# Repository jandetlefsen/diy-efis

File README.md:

# diy-efis
Experimental Aircraft Avionics based on CAN Aerospace

This repository is the public code and design store for the Kotuku Aerospace http://www.kotuku.aero contributed avionics project.

New: Facebook page created:

https://www.facebook.com/diyefis/

This project has designs from 2016 that have been tested.

The project has 3 core streams:

** diy-efis **
Portable C code that implements a full graphical display for avionics that can run on very low power devices.  The development environment is Eclipse on Linux or Visual Studio on Windows

** Embedded devices **
All diy-efis hardware devices are based on a common hardware family, the dsPIC33EP series from Microchip.  These devices are programmed in C and have the core I/O functions needed by the CANFly systems.  There is a common operating system and I/O drivers for most peripherals.

** Hardware Designs **
All diy-efis hardware designs are open source and are provided in Eagle PCB format.  They are designed to be very low cost 2 sided PCB's that can be hand assembled by a enthusiest.  Kotuku Aerospace will sell boards, partial kits, full kits or assembled hardware based on these designs.

diy-efis is managed by Kotuku Aerospace and any money made from selling kits is used to fund the hosting and designs.

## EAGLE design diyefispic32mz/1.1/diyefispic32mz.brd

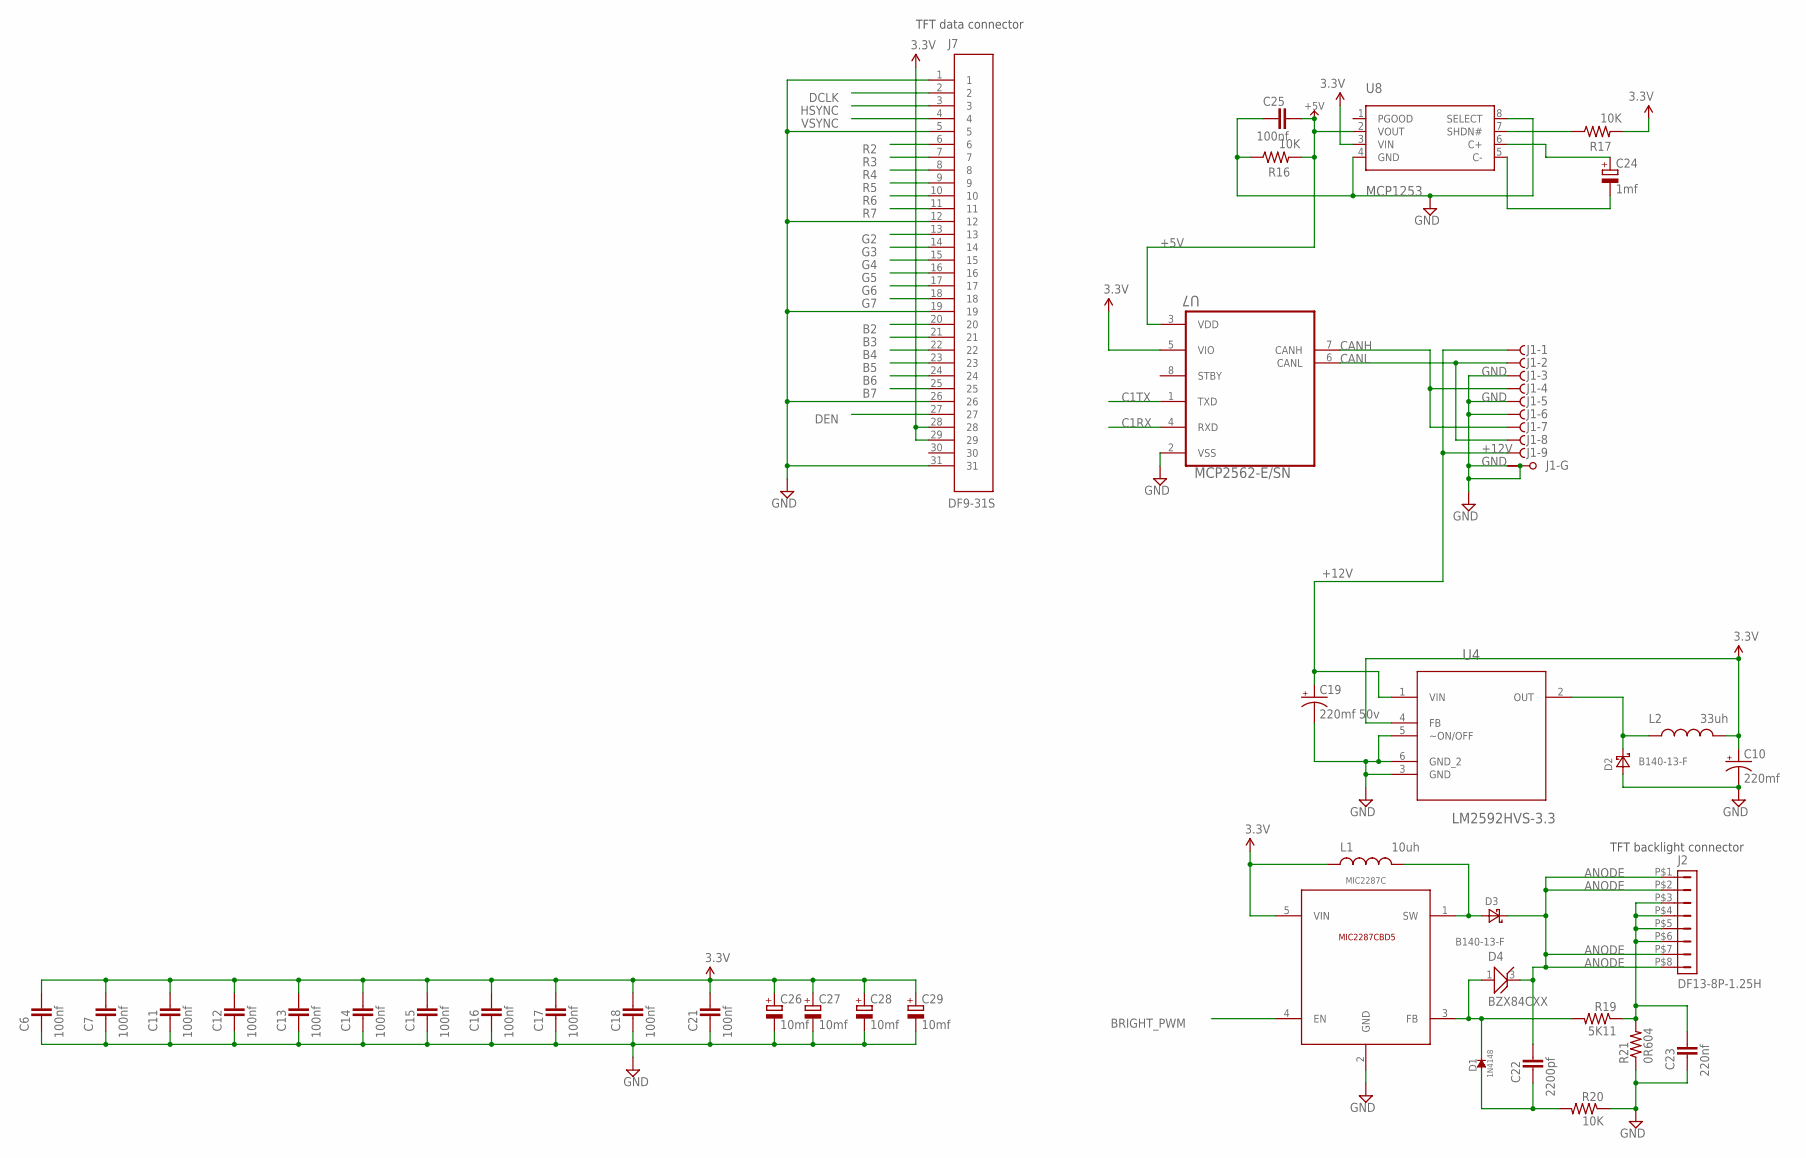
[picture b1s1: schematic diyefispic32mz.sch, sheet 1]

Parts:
C6, C7, C11, C12, C13, C14, C15, C16, C17, C18, C21, C25: 100nf; C805; PARTNO CL21F104ZBCNNNC
C10: 220mf; EIA7343; PARTNO T545X227M016ATE035
C19: 220mf 50v; EIA7343; PARTNO T545X227M016ATE035
C22: 2200pf; C805; PARTNO CL21B222KBANNNC
C23: 220nf; C805; PARTNO CL21F224ZBCNNNC
C24: 1mf; SMC_A; PARTNO F931C105MAA
C26, C27, C28, C29: 10mf; SMC_A; PARTNO T491A106K004AT
D1: 1N4148; SOD523; PARTNO 1N4148WT
D2, D3: B140-13-F; SMA; PARTNO B140-13-F
D4: BZX84CXX; SOT91P240X110-3N; PARTNO BZX84C30-7-F
J1: F09VPS; F09VP; PARTNO 3-1634222-2
J2: DF13-8P-1.25H; DF13A-8P-1.25H; PARTNO DF13A-8P-1.25H(50)
J7: DF9-31S; PARTNO DF9-31S-1V(32)
L1: 10uh; 1812; PARTNO VLF504015MT-100M
L2: 33uh; 1812; PARTNO LQH43MN330K03L
R16, R17, R20: 10K; 0603-RES; PARTNO RC0603FR-0710KL
R19: 5K11; 0603-RES; PARTNO RC0603FR-075K23L
R21: 0R604; 1812; PARTNO RL1218FK-070R604L
U4: LM2592HVS-3.3; TO170P1435X457-5N; PARTNO LM2592HVSX-3.3/NOPB
U7: MCP2562-E/SN; SOIC127P600X175-8N; PARTNO MCP2562-E/SN
U8: MCP1253; MSOP8; PARTNO MCP1253-33X50I/MS
U9: MIC2287C; SOT-23-5; PARTNO MIC2287CYD5-TR

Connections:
3.3V: C6.1, C7.1, C10.A (+), C11.1, C12.1, C13.1, C14.1, C15.1, C16.1, C17.1, C18.1, C21.1, C26.+, C27.+, C28.+, C29.+, J7.28, J7.29, L1.1, L2.2, R17.2, U4.4 (FB), U7.5 (VIO), U8.3 (VIN), U9.5 (VIN); also elsewhere on the board
+5V: C25.1, R16.2, U7.3 (VDD), U8.2 (VOUT); also elsewhere on the board
+12V: C19.A (+), J1.1 (F), J1.9 (F), U4.1 (VIN)
ANODE: C22.1, D3.C, D4.3 (CATHODE), J2.P$1 (1), J2.P$2 (2), J2.P$7 (7), J2.P$8 (8)
B2: J7.20; also elsewhere on the board
B3: J7.21; also elsewhere on the board
B4: J7.22; also elsewhere on the board
B5: J7.23; also elsewhere on the board
B6: J7.24; also elsewhere on the board
B7: J7.25; also elsewhere on the board
BRIGHT_PWM: U9.4 (EN); also elsewhere on the board
C1RX: U7.4 (RXD); also elsewhere on the board
C1TX: U7.1 (TXD); also elsewhere on the board
CANH: J1.4 (F), J1.7 (F), U7.7 (CANH)
CANL: J1.2 (F), J1.8 (F), U7.6 (CANL)
DCLK: J7.2; also elsewhere on the board
DEN: J7.27; also elsewhere on the board
G2: J7.13; also elsewhere on the board
G3: J7.14; also elsewhere on the board
G4: J7.15; also elsewhere on the board
G5: J7.16; also elsewhere on the board
G6: J7.17; also elsewhere on the board
G7: J7.18; also elsewhere on the board
GND: C6.2, C7.2, C10.C (-), C11.2, C12.2, C13.2, C14.2, C15.2, C16.2, C17.2, C18.2, C19.C (-), C21.2, C23.2, C25.2, C26.-, C27.-, C28.-, C29.-, D2.A, J1.3 (F), J1.5 (F), J1.6 (F), J1.G1, J1.G2, J7.1, J7.5, J7.12, J7.19, J7.26, J7.31, R16.1, R20.1, R21.1, U4.3 (GND), U4.5 (~ON/OFF), U4.6 (GND_2), U7.2 (VSS), U8.4 (GND), U8.8 (SELECT), U9.2 (GND); also elsewhere on the board
HSYNC: J7.3; also elsewhere on the board
unnamed: C23.1, J2.P$3 (3), J2.P$4 (4), J2.P$5 (5), J2.P$6 (6), R19.1, R21.2
unnamed: D2.C, L2.1, U4.2 (OUT)
unnamed: R17.1, U8.7 (SHDN#)
unnamed: C24.-, U8.5 (C-)
unnamed: C24.+, U8.6 (C+)
unnamed: D3.A, L1.2, U9.1 (SW)
unnamed: D1.C, D4.1 (ANODE), R19.2, U9.3 (FB)
unnamed: C22.2, D1.A, R20.2
R2: J7.6; also elsewhere on the board
R3: J7.7; also elsewhere on the board
R4: J7.8; also elsewhere on the board
R5: J7.9; also elsewhere on the board
R6: J7.10; also elsewhere on the board
R7: J7.11; also elsewhere on the board
VSYNC: J7.4; also elsewhere on the board

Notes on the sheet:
TFT data connector
TFT backlight connector

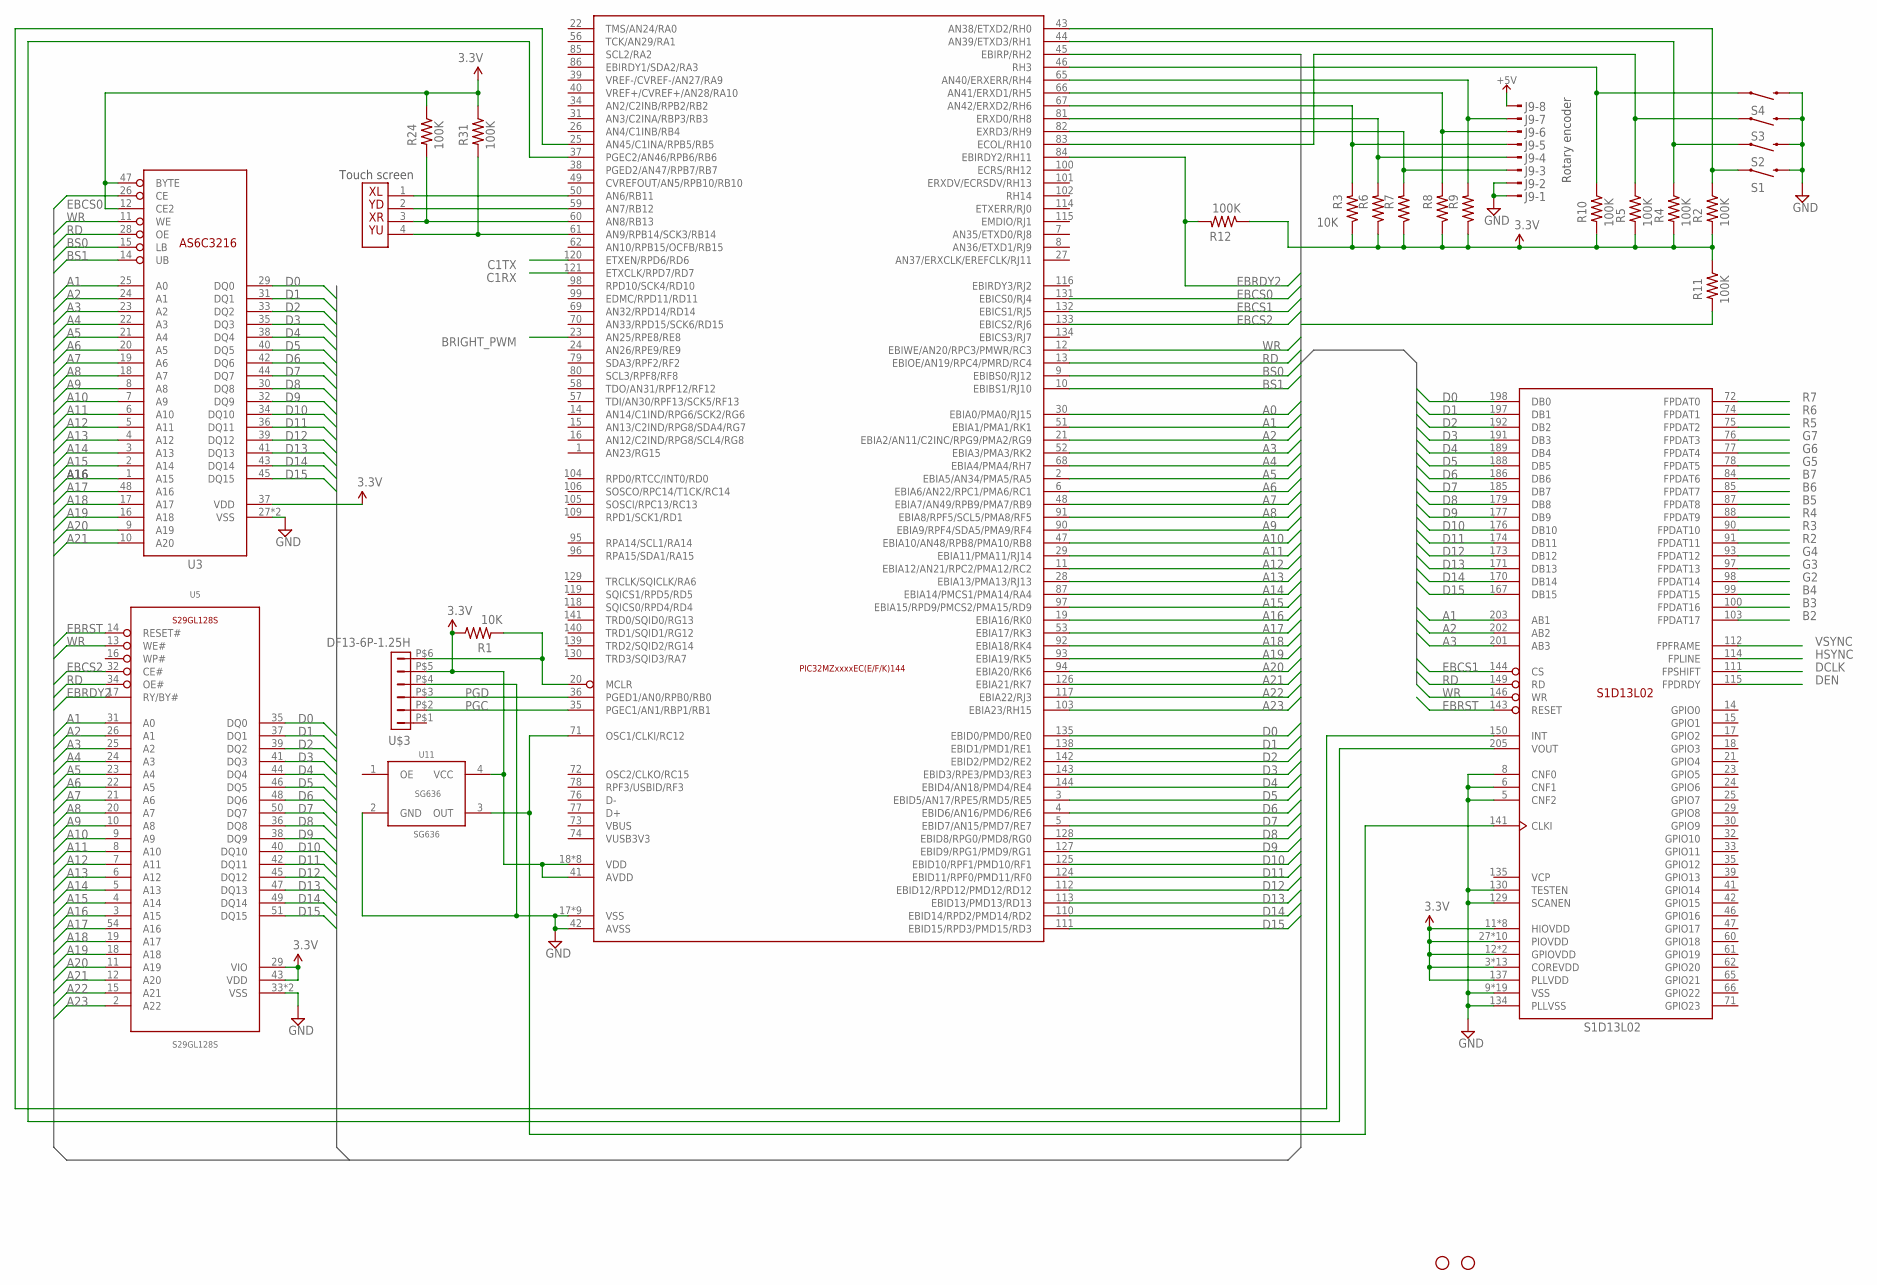
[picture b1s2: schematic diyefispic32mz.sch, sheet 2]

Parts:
J3: XF3M(1)-0415-1B; PARTNO XF3M(1)-0415-1B
J9: MTOP-8; PARTNO 7-215079-8
R1, R3, R6, R7, R8, R9: 10K; 0603-RES; PARTNO RC0603FR-0710KL
R2, R4, R5, R10, R11, R24, R31: 100K; 0603-RES; PARTNO RC0603JR-07100KL
R12: 100K; 0603-RES; PARTNO RC0603FR-0710KL
S1, S2, S3, S4: SWITCH-MOMENTARY-2SMD-4; TACTILE_SWITCH_TALL; PARTNO MJTP1138BTR
STANDOFF1, STANDOFF2: STAND-OFF; PARTNO *
U1: PIC32MZXXXXEC(E/F/K)144; TQFP-144; PARTNO PIC32MZ2048ECH144-I/PH
U2: S1D13L02; QFP208; PARTNO S1D13L02F00A100
U3: AS6C3216; TSOP48; PARTNO AS6C3216-55TIN
U5: S29GL128S; TSOP-56; PARTNO S29GL128S90TFI010
U11: SG636; PARTNO SG-636PCE 10.000MHZ
U$3: DF13-6P-1.25H; DF13A-6P-1.25H; PARTNO DF13A-6P-1.25H(20)

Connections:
3.3V: R1.1, R2.2, R3.1, R4.2, R5.2, R6.1, R7.1, R8.1, R9.1, R10.2, R11.1, R12.1, R24.1, R31.1, U1.18 (VDD), U1.33 (VDD), U1.41 (AVDD), U1.55 (VDD), U1.64 (VDD), U1.88 (VDD), U1.107 (VDD), U1.122 (VDD), U1.137 (VDD), U2.3 (COREVDD), U2.11 (HIOVDD), U2.12 (GPIOVDD), U2.26 (GPIOVDD), U2.27 (PIOVDD), U2.36 (PIOVDD), U2.38 (COREVDD), U2.45 (COREVDD), U2.48 (PIOVDD), U2.59 (PIOVDD), U2.68 (PIOVDD), U2.79 (PIOVDD), U2.82 (COREVDD), U2.94 (COREVDD), U2.96 (PIOVDD), U2.106 (PIOVDD), U2.119 (COREVDD), U2.121 (PIOVDD), U2.127 (PIOVDD), U2.128 (COREVDD), U2.133 (COREVDD), U2.137 (PLLVDD), U2.138 (HIOVDD), U2.148 (HIOVDD), U2.151 (HIOVDD), U2.152 (COREVDD), U2.157 (HIOVDD), U2.163 (COREVDD), U2.168 (HIOVDD), U2.181 (COREVDD), U2.184 (HIOVDD), U2.194 (COREVDD), U2.204 (COREVDD), U2.208 (HIOVDD), U3.12 (CE2), U3.37 (VDD), U3.47 (BYTE), U5.29 (VIO), U5.43 (VDD), U11.4 (VCC), U$3.P$5 (5); also elsewhere on the board
!MCLR: R1.2, U1.20 (MCLR), U$3.P$6 (6)
+5V: J9.8; also elsewhere on the board
A0: U1.30 (EBIA0/PMA0/RJ15)
A1: U1.51 (EBIA1/PMA1/RK1), U2.203 (AB1), U3.25 (A0), U5.31 (A0)
A2: U1.21 (EBIA2/AN11/C2INC/RPG9/PMA2/RG9), U2.202 (AB2), U3.24 (A1), U5.26 (A1)
A3: U1.52 (EBIA3/PMA3/RK2), U2.201 (AB3), U3.23 (A2), U5.25 (A2)
A4: U1.68 (EBIA4/PMA4/RH7), U3.22 (A3), U5.24 (A3)
A5: U1.2 (EBIA5/AN34/PMA5/RA5), U3.21 (A4), U5.23 (A4)
A6: U1.6 (EBIA6/AN22/RPC1/PMA6/RC1), U3.20 (A5), U5.22 (A5)
A7: U1.48 (EBIA7/AN49/RPB9/PMA7/RB9), U3.19 (A6), U5.21 (A6)
A8: U1.91 (EBIA8/RPF5/SCL5/PMA8/RF5), U3.18 (A7), U5.20 (A7)
A9: U1.90 (EBIA9/RPF4/SDA5/PMA9/RF4), U3.8 (A8), U5.10 (A8)
A10: U1.47 (EBIA10/AN48/RPB8/PMA10/RB8), U3.7 (A9), U5.9 (A9)
A11: U1.29 (EBIA11/PMA11/RJ14), U3.6 (A10), U5.8 (A10)
A12: U1.11 (EBIA12/AN21/RPC2/PMA12/RC2), U3.5 (A11), U5.7 (A11)
A13: U1.28 (EBIA13/PMA13/RJ13), U3.4 (A12), U5.6 (A12)
A14: U1.87 (EBIA14/PMCS1/PMA14/RA4), U3.3 (A13), U5.5 (A13)
A15: U1.97 (EBIA15/RPD9/PMCS2/PMA15/RD9), U3.2 (A14), U5.4 (A14)
A16: U1.19 (EBIA16/RK0), U3.1 (A15), U5.3 (A15)
A17: U1.53 (EBIA17/RK3), U3.48 (A16), U5.54 (A16)
A18: U1.92 (EBIA18/RK4), U3.17 (A17), U5.19 (A17)
A19: U1.93 (EBIA19/RK5), U3.16 (A18), U5.18 (A18)
A20: U1.94 (EBIA20/RK6), U3.9 (A19), U5.11 (A19)
A21: U1.126 (EBIA21/RK7), U3.10 (A20), U5.12 (A20)
A22: U1.117 (EBIA22/RJ3), U5.15 (A21)
A23: U1.103 (EBIA23/RH15), U5.2 (A22)
B2: U2.103 (FPDAT17); also elsewhere on the board
B3: U2.100 (FPDAT16); also elsewhere on the board
B4: U2.99 (FPDAT15); also elsewhere on the board
B5: U2.87 (FPDAT8); also elsewhere on the board
B6: U2.85 (FPDAT7); also elsewhere on the board
B7: U2.84 (FPDAT6); also elsewhere on the board
BRIGHT_PWM: U1.23 (AN25/RPE8/RE8); also elsewhere on the board
BS0: U1.9 (EBIBS0/RJ12), U3.15 (LB)
BS1: U1.10 (EBIBS1/RJ10), U3.14 (UB)
C1RX: U1.121 (ETXCLK/RPD7/RD7); also elsewhere on the board
C1TX: U1.120 (ETXEN/RPD6/RD6); also elsewhere on the board
D0: U1.135 (EBID0/PMD0/RE0), U2.198 (DB0), U3.29 (DQ0), U5.35 (DQ0)
D1: U1.138 (EBID1/PMD1/RE1), U2.197 (DB1), U3.31 (DQ1), U5.37 (DQ1)
D2: U1.142 (EBID2/PMD2/RE2), U2.192 (DB2), U3.33 (DQ2), U5.39 (DQ2)
D3: U1.143 (EBID3/RPE3/PMD3/RE3), U2.191 (DB3), U3.35 (DQ3), U5.41 (DQ3)
D4: U1.144 (EBID4/AN18/PMD4/RE4), U2.189 (DB4), U3.38 (DQ4), U5.44 (DQ4)
D5: U1.3 (EBID5/AN17/RPE5/RMD5/RE5), U2.188 (DB5), U3.40 (DQ5), U5.46 (DQ5)
D6: U1.4 (EBID6/AN16/PMD6/RE6), U2.186 (DB6), U3.42 (DQ6), U5.48 (DQ6)
D7: U1.5 (EBID7/AN15/PMD7/RE7), U2.185 (DB7), U3.44 (DQ7), U5.50 (DQ7)
D8: U1.128 (EBID8/RPG0/PMD8/RG0), U2.179 (DB8), U3.30 (DQ8), U5.36 (DQ8)
D9: U1.127 (EBID9/RPG1/PMD9/RG1), U2.177 (DB9), U3.32 (DQ9), U5.38 (DQ9)
D10: U1.125 (EBID10/RPF1/PMD10/RF1), U2.176 (DB10), U3.34 (DQ10), U5.40 (DQ10)
D11: U1.124 (EBID11/RPF0/PMD11/RF0), U2.174 (DB11), U3.36 (DQ11), U5.42 (DQ11)
D12: U1.112 (EBID12/RPD12/PMD12/RD12), U2.173 (DB12), U3.39 (DQ12), U5.45 (DQ12)
D13: U1.113 (EBID13/PMD13/RD13), U2.171 (DB13), U3.41 (DQ13), U5.47 (DQ13)
D14: U1.110 (EBID14/RPD2/PMD14/RD2), U2.170 (DB14), U3.43 (DQ14), U5.49 (DQ14)
D15: U1.111 (EBID15/RPD3/PMD15/RD3), U2.167 (DB15), U3.45 (DQ15), U5.51 (DQ15)
DCLK: U2.111 (FPSHIFT); also elsewhere on the board
DEN: U2.115 (FPDRDY); also elsewhere on the board
EBCS0: U1.131 (EBICS0/RJ4), U3.26 (CE)
EBCS1: U1.132 (EBICS1/RJ5), U2.144 (CS)
EBCS2: U1.133 (EBICS2/RJ6), U5.32 (CE#)
EBRDY2: R12.2, U1.84 (EBIRDY2/RH11), U5.17 (RY/BY#)
EBRST: R11.2, U1.45 (EBIRP/RH2), U2.143 (RESET), U5.14 (RESET#)
G2: U2.98 (FPDAT14); also elsewhere on the board
G3: U2.97 (FPDAT13); also elsewhere on the board
G4: U2.93 (FPDAT12); also elsewhere on the board
G5: U2.78 (FPDAT5); also elsewhere on the board
G6: U2.77 (FPDAT4); also elsewhere on the board
G7: U2.76 (FPDAT3); also elsewhere on the board
GND: J9.1, J9.2, S1.B2 (2), S2.B2 (2), S3.B2 (2), S4.B2 (2), U1.17 (VSS), U1.32 (VSS), U1.42 (AVSS), U1.54 (VSS), U1.63 (VSS), U1.75 (VSS), U1.89 (VSS), U1.108 (VSS), U1.123 (VSS), U1.136 (VSS), U2.5 (CNF2), U2.6 (CNF1), U2.8 (CNF0), U2.9 (VSS), U2.20 (VSS), U2.28 (VSS), U2.44 (VSS), U2.50 (VSS), U2.58 (VSS), U2.69 (VSS), U2.80 (VSS), U2.95 (VSS), U2.109 (VSS), U2.120 (VSS), U2.129 (SCANEN), U2.130 (TESTEN), U2.132 (VSS), U2.134 (PLLVSS), U2.140 (VSS), U2.147 (VSS), U2.155 (VSS), U2.166 (VSS), U2.187 (VSS), U2.200 (VSS), U2.206 (VSS), U3.27 (VSS), U3.46 (VSS), U5.33 (VSS), U5.52 (VSS), U11.2 (GND), U$3.P$4 (4); also elsewhere on the board
GPG0: J9.7, R9.2, U1.65 (AN40/ERXERR/RH4)
GPG1: J9.6, R8.2, U1.66 (AN41/ERXD1/RH5)
GPG2: J9.3, R7.2, U1.82 (EXRD3/RH9)
GPG3: J9.4, R6.2, U1.81 (ERXD0/RH8)
GPG4: J9.5, R3.2, U1.67 (AN42/ERXD2/RH6)
HSYNC: U2.114 (FPLINE); also elsewhere on the board
unnamed: U1.71 (OSC1/CLKI/RC12), U2.141 (CLKI), U11.3 (OUT)
unnamed: J3.1, U1.50 (AN6/RB11)
unnamed: J3.2, U1.59 (AN7/RB12)
unnamed: J3.3, R24.2, U1.60 (AN8/RB13)
unnamed: J3.4, R31.2, U1.61 (AN9/RPB14/SCK3/RB14)
unnamed: R2.1, S1.A2 (1), U1.43 (AN38/ETXD2/RH0)
unnamed: R4.1, S2.A2 (1), U1.44 (AN39/ETXD3/RH1)
unnamed: R5.1, S3.A2 (1), U1.83 (ECOL/RH10)
unnamed: R10.1, S4.A2 (1), U1.46 (RH3)
PGC: U1.35 (PGEC1/AN1/RBP1/RB1), U$3.P$2 (2)
PGD: U1.36 (PGED1/AN0/RPB0/RB0), U$3.P$3 (3)
R2: U2.91 (FPDAT11); also elsewhere on the board
R3: U2.90 (FPDAT10); also elsewhere on the board
R4: U2.88 (FPDAT9); also elsewhere on the board
R5: U2.75 (FPDAT2); also elsewhere on the board
R6: U2.74 (FPDAT1); also elsewhere on the board
R7: U2.72 (FPDAT0); also elsewhere on the board
RD: U1.13 (EBIOE/AN19/RPC4/PMRD/RC4), U2.149 (RD), U3.28 (OE), U5.34 (OE#)
VID_INT: U1.25 (AN45/C1INA/RPB5/RB5), U2.150 (INT)
VID_VSYNC: U1.37 (PGEC2/AN46/RPB6/RB6), U2.205 (VOUT)
VSYNC: U2.112 (FPFRAME); also elsewhere on the board
WR: U1.12 (EBIWE/AN20/RPC3/PMWR/RC3), U2.146 (WR), U3.11 (WE), U5.13 (WE#)

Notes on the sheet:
Touch screen
Rotary encoder

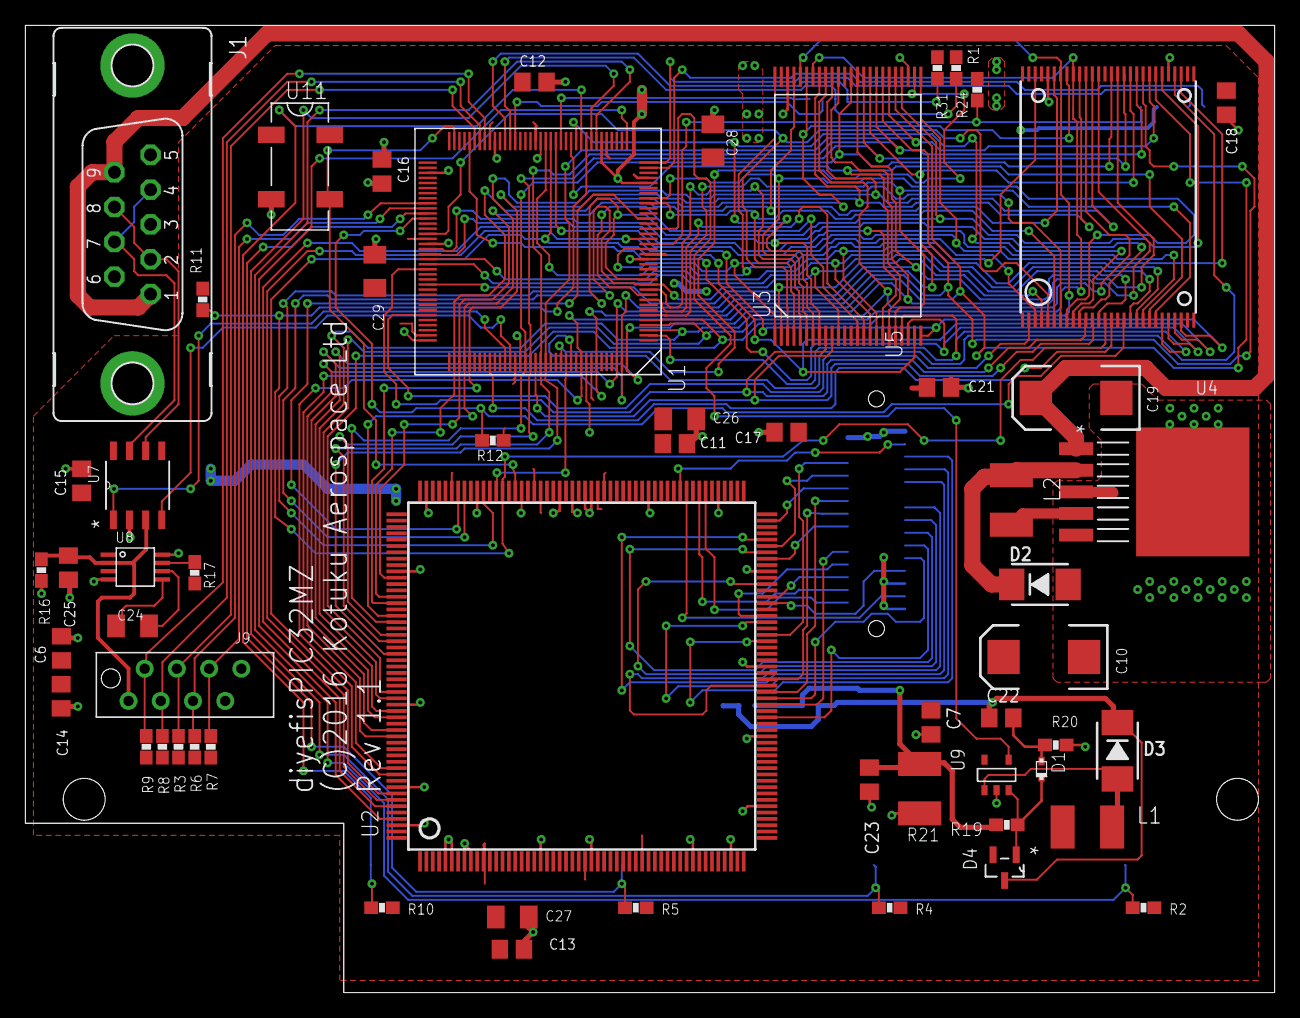
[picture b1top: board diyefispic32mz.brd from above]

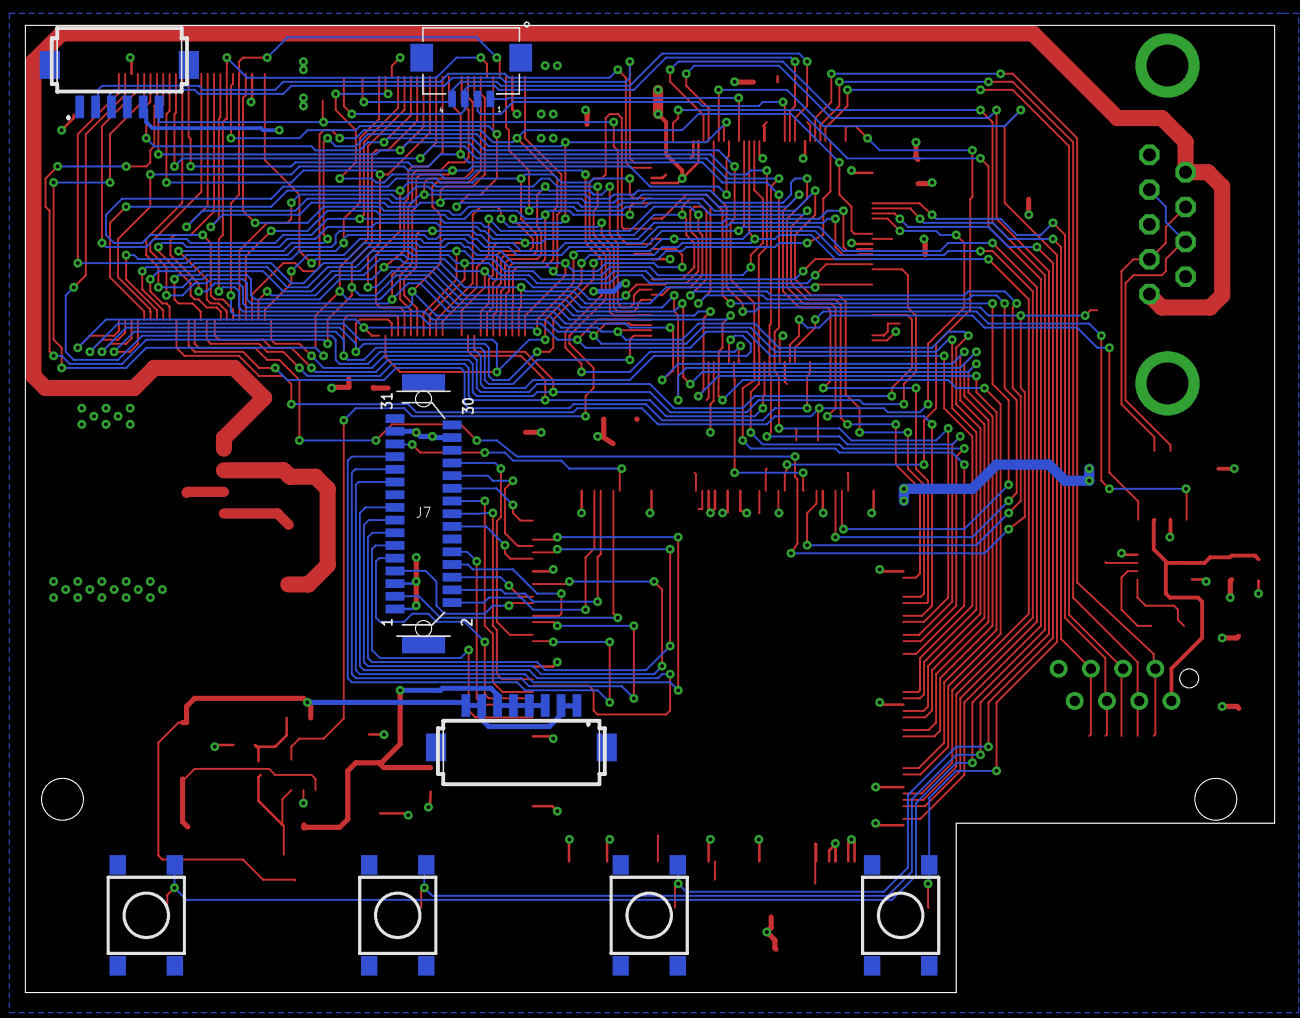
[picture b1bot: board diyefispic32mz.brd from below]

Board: 2 copper layers, 98.4 x 76.2 mm, 67 parts (8 on the bottom side), 107 nets.

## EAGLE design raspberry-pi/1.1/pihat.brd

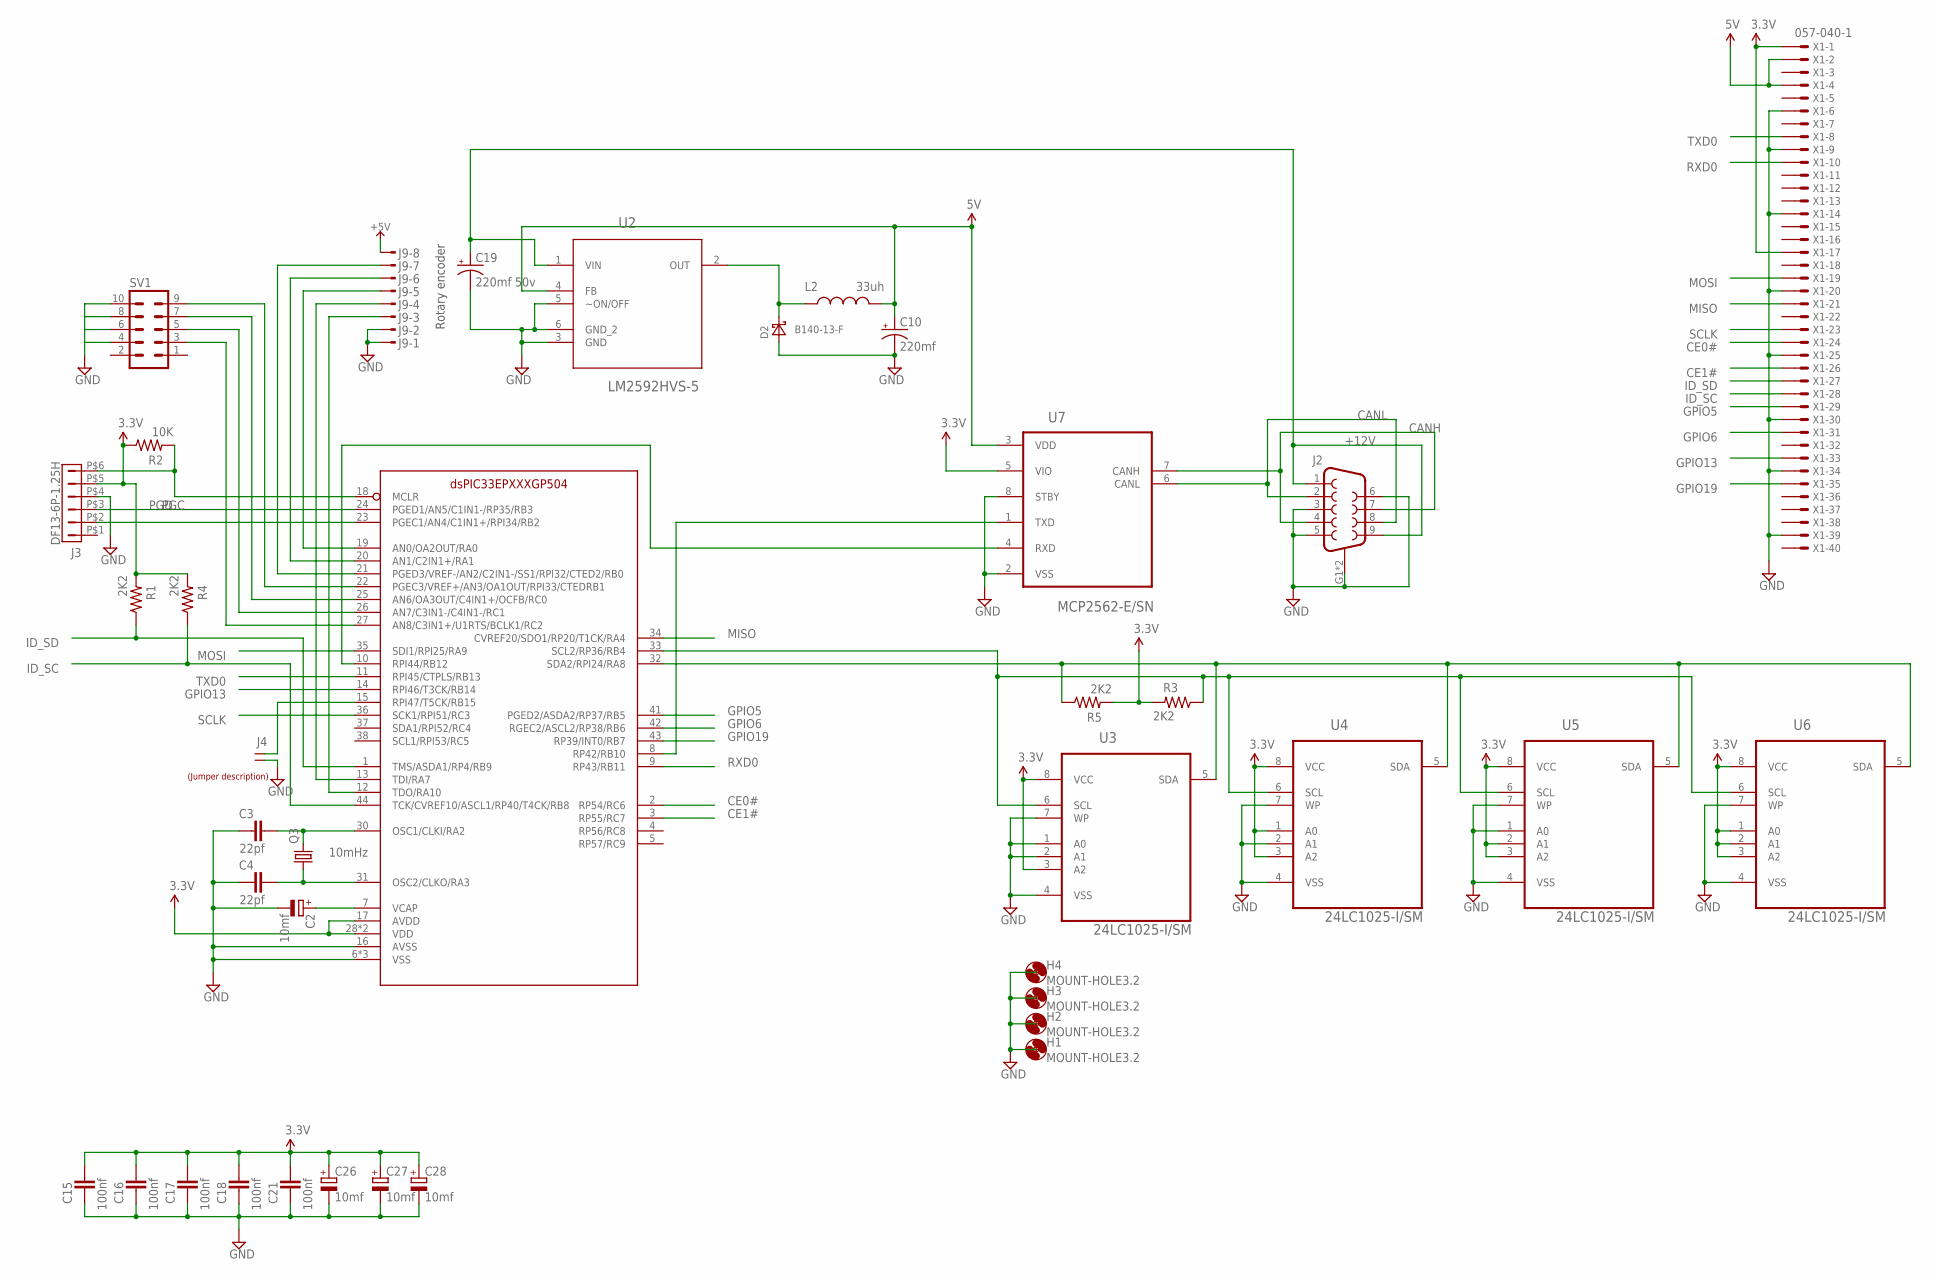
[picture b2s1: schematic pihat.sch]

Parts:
C2, C26, C27, C28: 10mf; SMC_A; PARTNO T491A106K004AT
C3, C4: 22pf; C805; PARTNO C0805C220J5GACTU
C10: 220mf; EIA7343; PARTNO T545X227M016ATE035
C15, C16, C17, C18, C21: 100nf; C805; PARTNO CL21F104ZBCNNNC
C19: 220mf 50v; EIA7343; PARTNO T545X227M016ATE035
D2: B140-13-F; SMA; PARTNO B140-13-F
H1, H2, H3, H4: MOUNT-HOLE3.2; 3,2
J2: DB9FEMALE; DB9; PARTNO 1734354-2
J3: DF13-6P-1.25H; DF13A-6P-1.25H; PARTNO DF13A-6P-1.25H(20)
J4: JUMPER-1X2; PARTNO M20-9770246
J9: MTOP-8; PARTNO 7-215079-8
L2: 33uh; 1812; PARTNO LQH43MN330K03L
Q3: 10mHz; HC49/S; PARTNO ATS100B-E
R1, R3, R4, R5: 2K2; 0603-RES; PARTNO RC0603FR-072K2L
R2: 10K; 0603-RES; PARTNO RC0603FR-0710KL
SV1: MA05-2
U1: DSPIC33EPXXXGP504; TQFP44; PARTNO DSPIC33EP512GP504-I/PT
U2: LM2592HVS-5; TO170P1435X457-5N; PARTNO LM2592HVSX-3.3/NOPB
U3, U4, U5, U6: 24LC1025-I/SM; SOIC8-N_MC; PARTNO 24LC1025T-I/SN
U7: MCP2562-E/SN; SOIC-8N; PARTNO MCP2562-E/SN
U$1: LABEL_JUMPER_1X2; JUMP2_DESC
X1: 057-040-1

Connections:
3.3V: C15.1, C16.1, C17.1, C18.1, C21.1, C26.+, C27.+, C28.+, J3.P$5 (5), R1.2, R2.1, R3.2, R4.2, R5.2, U1.17 (AVDD), U1.28 (VDD), U1.40 (VDD), U3.3 (A2), U3.8 (VCC), U4.1 (A0), U4.3 (A2), U4.8 (VCC), U5.2 (A1), U5.3 (A2), U5.8 (VCC), U6.1 (A0), U6.2 (A1), U6.3 (A2), U6.8 (VCC), U7.5 (VIO), X1.1, X1.17
5V: C10.A (+), L2.2, U2.4 (FB), U7.3 (VDD), X1.2, X1.4
!MCLR: J3.P$6 (6), R2.2, U1.18 (MCLR)
+5V: J9.8
+12V: C19.A (+), J2.1, J2.9, U2.1 (VIN)
CANH: J2.4, J2.7, U7.7 (CANH)
CANL: J2.2, J2.8, U7.6 (CANL)
CE0#: U1.2 (RP54/RC6), X1.24
CE1#: U1.3 (RP55/RC7), X1.26
GND: C2.-, C3.2, C4.2, C10.C (-), C15.2, C16.2, C17.2, C18.2, C19.C (-), C21.2, C26.-, C27.-, C28.-, D2.A, J2.3, J2.5, J2.6, J2.G1 (SHIELD), J2.G2 (SHIELD), J3.P$4 (4), J4.2, J9.1, J9.2, SV1.4, SV1.6, SV1.8, SV1.10, U1.6 (VSS), U1.16 (AVSS), U1.29 (VSS), U1.39 (VSS), U2.3 (GND), U2.5 (~ON/OFF), U2.6 (GND_2), U3.1 (A0), U3.2 (A1), U3.4 (VSS), U3.7 (WP), U4.2 (A1), U4.4 (VSS), U4.7 (WP), U5.1 (A0), U5.4 (VSS), U5.7 (WP), U6.4 (VSS), U6.7 (WP), U7.2 (VSS), U7.8 (STBY), X1.6, X1.9, X1.14, X1.20, X1.25, X1.30, X1.34, X1.39
GPIO5: U1.41 (PGED2/ASDA2/RP37/RB5), X1.29
GPIO6: U1.42 (RGEC2/ASCL2/RP38/RB6), X1.31
GPIO13: U1.14 (RPI46/T3CK/RB14), X1.33
GPIO19: U1.43 (RP39/INT0/RB7), X1.35
ID_SC: R4.1, U1.44 (TCK/CVREF10/ASCL1/RP40/T4CK/RB8), X1.28
ID_SD: R1.1, U1.1 (TMS/ASDA1/RP4/RB9), X1.27
MISO: U1.34 (CVREF20/SDO1/RP20/T1CK/RA4), X1.21
MOSI: U1.35 (SDI1/RPI25/RA9), X1.19
unnamed: J9.3, U1.12 (TDO/RA10)
unnamed: J9.4, U1.13 (TDI/RA7)
unnamed: J9.5, U1.19 (AN0/OA2OUT/RA0)
unnamed: J9.6, U1.20 (AN1/C2IN1+/RA1)
unnamed: J9.7, U1.21 (PGED3/VREF-/AN2/C2IN1-/SS1/RPI32/CTED2/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)
unnamed: SV1.9, U1.22 (PGEC3/VREF+/AN3/OA1OUT/RPI33/CTEDRB1)
unnamed: SV1.7, U1.25 (AN6/OA3OUT/C4IN1+/OCFB/RC0)
unnamed: SV1.5, U1.26 (AN7/C3IN1-/C4IN1-/RC1)
unnamed: SV1.3, U1.27 (AN8/C3IN1+/U1RTS/BCLK1/RC2)
unnamed: D2.C, L2.1, U2.2 (OUT)
unnamed: C3.1, Q3.2, U1.30 (OSC1/CLKI/RA2)
unnamed: U1.10 (RPI44/RB12), U7.4 (RXD)
unnamed: C2.+, U1.7 (VCAP)
unnamed: U1.8 (RP42/RB10), U7.1 (TXD)
unnamed: C4.1, Q3.1, U1.31 (OSC2/CLKO/RA3)
PGC: J3.P$2 (2), U1.23 (PGEC1/AN4/C1IN1+/RPI34/RB2)
PGD: J3.P$3 (3), U1.24 (PGED1/AN5/C1IN1-/RP35/RB3)
RESET#: J4.1, U1.15 (RPI47/T5CK/RB15)
RXD0: U1.9 (RP43/RB11), X1.10
SCL: R3.1, U1.33 (SCL2/RP36/RB4), U3.6 (SCL), U4.6 (SCL), U5.6 (SCL), U6.6 (SCL)
SCLK: U1.36 (SCK1/RPI51/RC3), X1.23
SDA: R5.1, U1.32 (SDA2/RPI24/RA8), U3.5 (SDA), U4.5 (SDA), U5.5 (SDA), U6.5 (SDA)
TXD0: U1.11 (RPI45/CTPLS/RB13), X1.8

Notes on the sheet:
Rotary encoder

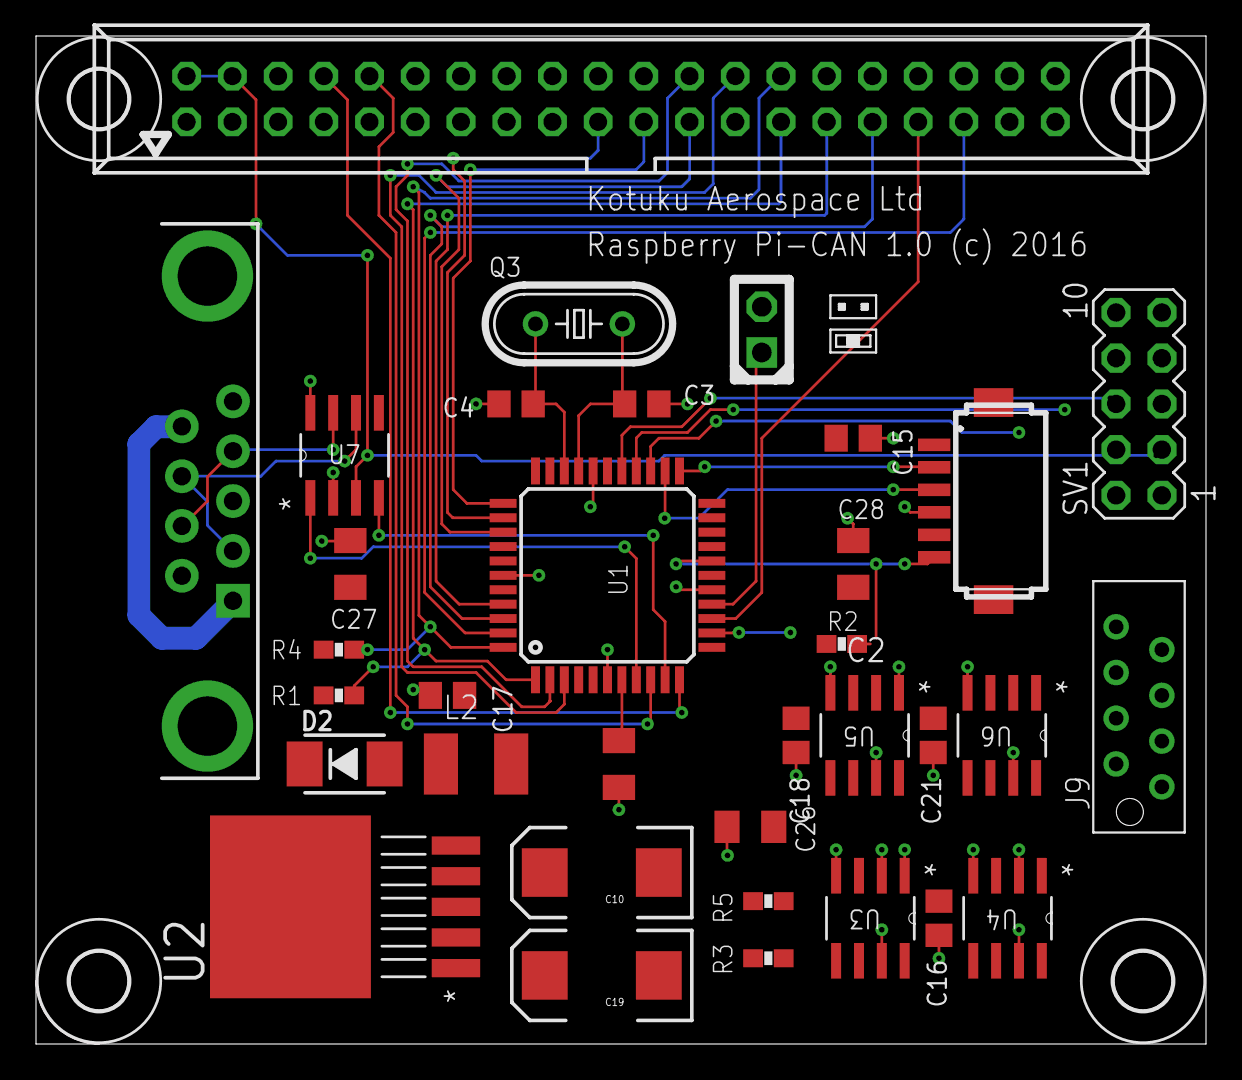
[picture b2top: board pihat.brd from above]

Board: 2 copper layers, 65.0 x 56.0 mm, 39 parts (0 on the bottom side), 40 nets.

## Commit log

2016-06-20 Create gh-pages branch via GitHub
2016-08-18 Added release 1.1 of pi-hat
2016-08-23 Fixed offset problem in AHRS
2016-10-21 Added pic32mz to project
2016-10-24 Revert "Added pic32mz to project"
    This reverts commit 8f4e1f7f0bb516d1dddae89f53fbf36136b80457.

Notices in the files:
diyefispic32mz/1.1/diyefispic32mz.brd:
(C)2016 Kotuku Aerospace Ltd
raspberry-pi/1.1/pihat.brd:
Raspberry Pi-CAN 1.0 (c) 2016
parts and their libraries:
SparkFun-Passives: Licensing: Creative Commons ShareAlike 4.0 International - https://creativecommons.org/licenses/by-sa/4.0
